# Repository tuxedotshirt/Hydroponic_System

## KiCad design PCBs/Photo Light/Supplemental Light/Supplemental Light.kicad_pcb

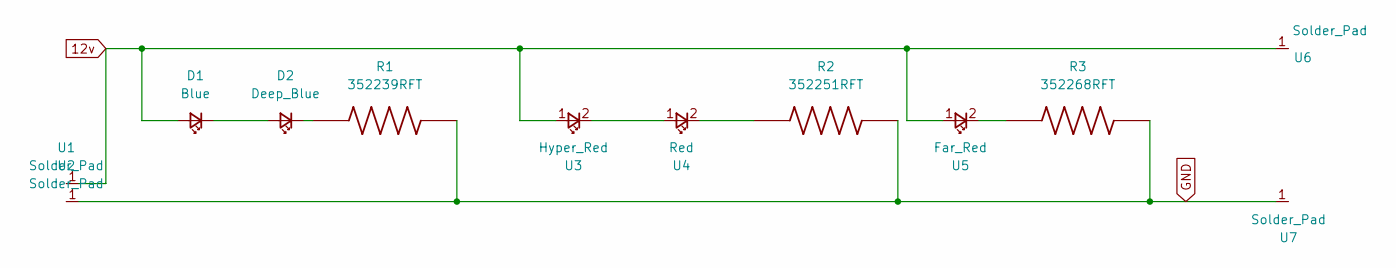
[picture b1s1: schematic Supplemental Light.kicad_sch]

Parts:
D1: Blue
D2: Deep_Blue; Deep Blue
R1: 352239RFT; RESC6332X120N
R2: 352251RFT; RESC6332X120N
R3: 352268RFT; RESC6332X120N
U1, U2, U6, U7: Solder_Pad; Solder Pad
U3: Hyper_Red; Hyper Red
U4: Red
U5: Far_Red; Far Red

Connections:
12v: D1.1 (A), U1.1, U3.1, U5.1, U6.1
GND: R1.2, R2.2, R3.2, U2.1, U7.1
unnamed: D1.2 (K), D2.1 (A)
unnamed: D2.2 (K), R1.1
unnamed: R2.1, U4.2
unnamed: U3.2, U4.1
unnamed: R3.1, U5.2

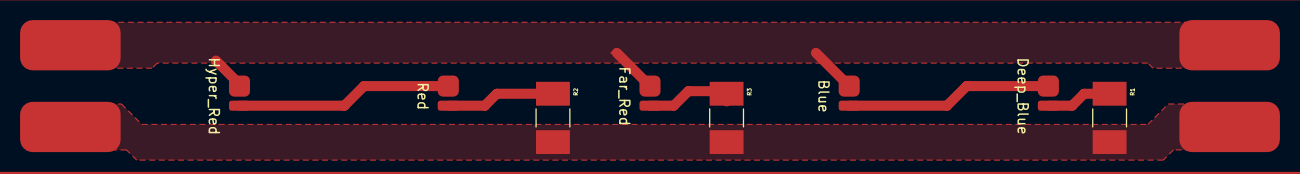
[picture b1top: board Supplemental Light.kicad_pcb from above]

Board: 2 copper layers, 12 parts (0 on the bottom side), 7 nets.

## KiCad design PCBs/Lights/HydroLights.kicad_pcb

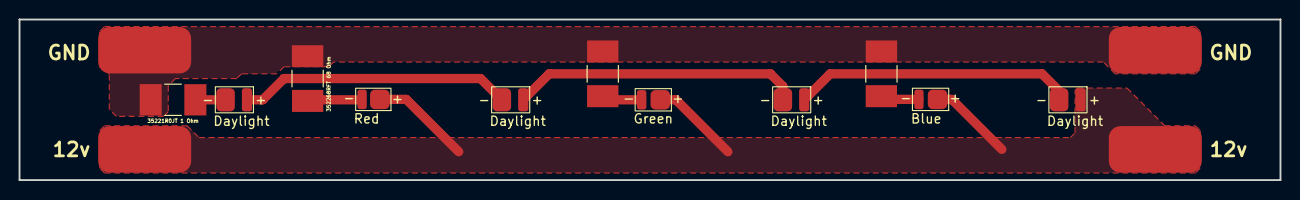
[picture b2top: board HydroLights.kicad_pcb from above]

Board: 2 copper layers, 135.6 x 17.3 mm, 15 parts (0 on the bottom side), 9 nets.

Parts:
R1: 352268RFT 68 Ohm; RESC6332X120N
R2, R4: 352262RFT 62 Ohm; RESC6332X120N
R3: 35221R0JT 1 Ohm; RESC6332X120N
U1, U2, U10, U11: Solder_Pad; Solder Pad
U3, U5, U7, U9: Daylight; 158303250A(Daylight)
U4: Red; 150283HS73103(Red)
U6: Blue; 150283BS73103(Blue)
U8: Green; 150283BS73103(Green)

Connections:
12v: U1.1, U3.2, U4.1, U6.1, U8.1, U10.1
GND: R1.2, R2.2, R3.1, R4.2, U2.1, U11.1
unnamed: R1.1, U4.2
unnamed: R2.1, U6.2
unnamed: R3.2, U9.1
unnamed: R4.1, U8.2
unnamed: U3.1, U5.2
unnamed: U5.1, U7.2
unnamed: U7.1, U9.2

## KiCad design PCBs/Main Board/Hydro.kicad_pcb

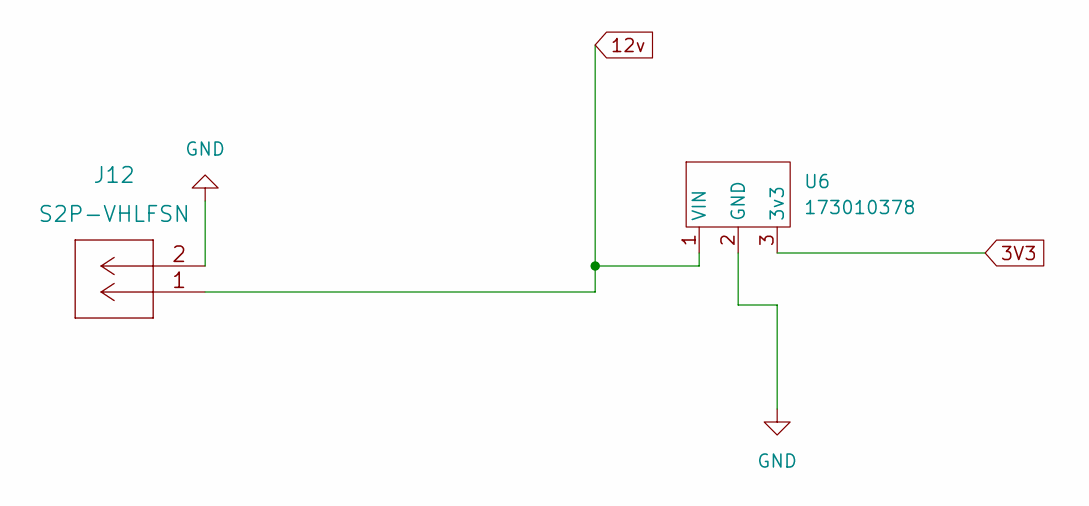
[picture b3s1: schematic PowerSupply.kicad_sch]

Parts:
J12: S2P-VHLFSN
U6: 173010378

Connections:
3V3: U6.3 (3v3); also elsewhere on the board
12v: J12.1, U6.1 (VIN); also elsewhere on the board
GND: J12.2, U6.2 (GND); also elsewhere on the board

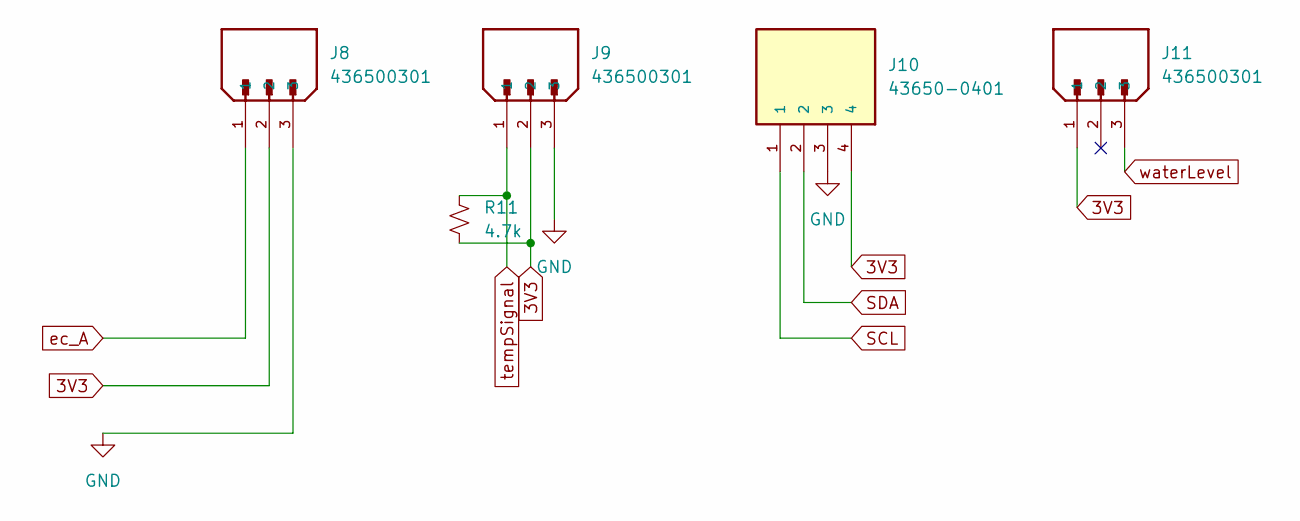
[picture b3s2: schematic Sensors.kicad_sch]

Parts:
J8, J9, J11: 436500301; MOLEX_436500301; PARTREV D7
J10: 43650-0401; MOLEX_43650-0401; PARTREV D7
R11: 4.7k; R_Axial_DIN0204_L3.6mm_D1.6mm_P7.62mm_Horizontal

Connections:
3V3: J8.2, J9.2, J10.4, J11.1, R11.2; also elsewhere on the board
GND: J8.3, J9.3, J10.3; also elsewhere on the board
SCL: J10.1; also elsewhere on the board
SDA: J10.2; also elsewhere on the board
ec_A: J8.1; also elsewhere on the board
tempSignal: J9.1, R11.1; also elsewhere on the board
waterLevel: J11.3; also elsewhere on the board

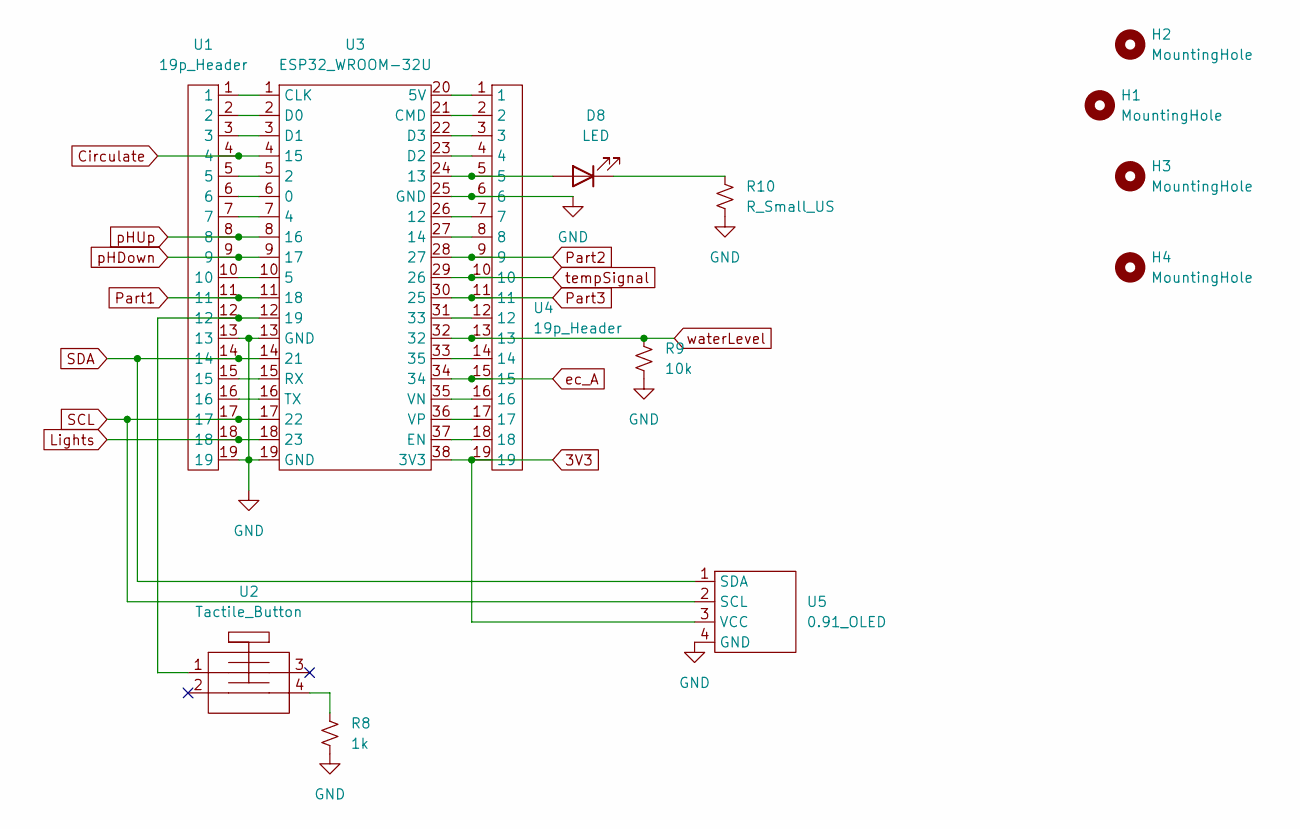
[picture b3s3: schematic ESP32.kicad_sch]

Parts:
D8: LED; LED_D5.0mm
H1, H2, H3, H4: MountingHole; Mounting Hole
R8: 1k; R_Axial_DIN0204_L3.6mm_D1.6mm_P7.62mm_Horizontal
R9: 10k; R_Axial_DIN0204_L3.6mm_D1.6mm_P7.62mm_Horizontal
R10: R_Small_US; R_Axial_DIN0204_L3.6mm_D1.6mm_P7.62mm_Horizontal
U1, U4: 19p_Header; 19p Header
U2: Tactile_Button
U3: ESP32_WROOM-32U; ESP32-WROOM-32U
U5: 0.91_OLED; 0.91 OLED

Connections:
3V3: U3.38 (3V3), U4.19, U5.3 (VCC); also elsewhere on the board
Circulate: U1.4, U3.4 (15); also elsewhere on the board
GND: R8.2, R9.2, R10.2, U1.13, U1.19, U3.13 (GND), U3.19 (GND), U3.25 (GND), U4.6, U5.4 (GND); also elsewhere on the board
Lights: U1.18, U3.18 (23); also elsewhere on the board
unnamed: D8.1 (K), R10.1
unnamed: D8.2 (A), U3.24 (13), U4.5
unnamed: R8.1, U2.4
unnamed: U1.1, U3.1 (CLK)
unnamed: U1.2, U3.2 (D0)
unnamed: U1.3, U3.3 (D1)
unnamed: U1.5, U3.5 (2)
unnamed: U1.6, U3.6 (0)
unnamed: U1.7, U3.7 (4)
unnamed: U1.10, U3.10 (5)
unnamed: U1.12, U2.1, U3.12 (19)
unnamed: U1.15, U3.15 (RX)
unnamed: U1.16, U3.16 (TX)
unnamed: U3.20 (5V), U4.1
unnamed: U3.21 (CMD), U4.2
unnamed: U3.22 (D3), U4.3
unnamed: U3.23 (D2), U4.4
unnamed: U3.26 (12), U4.7
unnamed: U3.27 (14), U4.8
unnamed: U3.31 (33), U4.12
unnamed: U3.33 (35), U4.14
unnamed: U3.35 (VN), U4.16
unnamed: U3.36 (VP), U4.17
unnamed: U3.37 (EN), U4.18
Part1: U1.11, U3.11 (18); also elsewhere on the board
Part2: U3.28 (27), U4.9; also elsewhere on the board
Part3: U3.30 (25), U4.11; also elsewhere on the board
SCL: U1.17, U3.17 (22), U5.2 (SCL); also elsewhere on the board
SDA: U1.14, U3.14 (21), U5.1 (SDA); also elsewhere on the board
ec_A: U3.34, U4.15; also elsewhere on the board
pHDown: U1.9, U3.9 (17); also elsewhere on the board
pHUp: U1.8, U3.8 (16); also elsewhere on the board
tempSignal: U3.29 (26), U4.10; also elsewhere on the board
waterLevel: R9.1, U3.32, U4.13; also elsewhere on the board

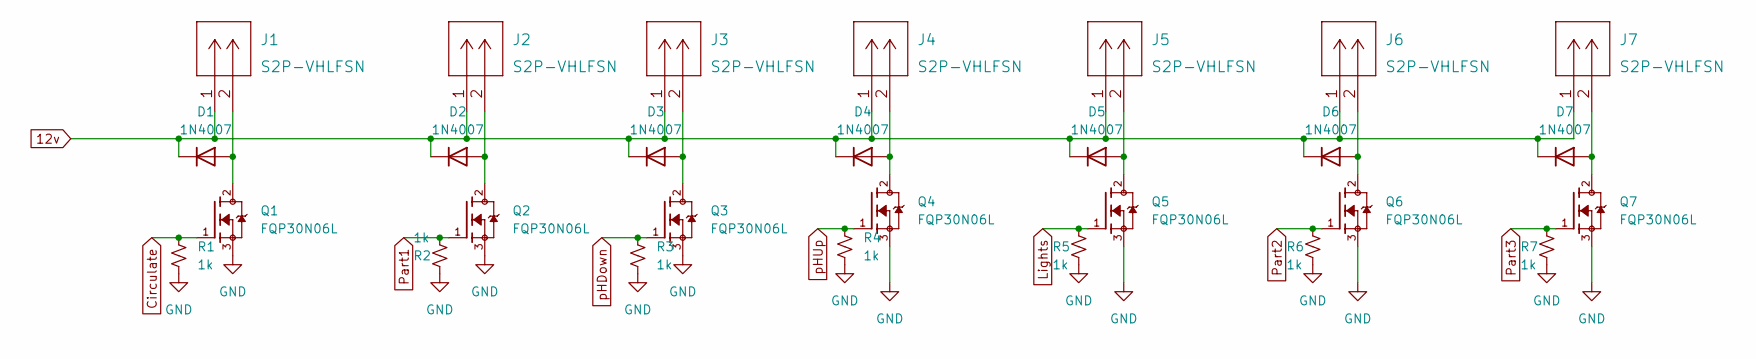
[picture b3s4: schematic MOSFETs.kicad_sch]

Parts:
D1, D2, D3, D4, D5, D6, D7: 1N4007; D_DO-41_SOD81_P10.16mm_Horizontal
J1, J2, J3, J4, J5, J6, J7: S2P-VHLFSN
Q1, Q2, Q3, Q4, Q5, Q6, Q7: FQP30N06L; TO220V
R1, R2, R3, R4, R5, R6, R7: 1k; R_Axial_DIN0207_L6.3mm_D2.5mm_P7.62mm_Horizontal

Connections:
12v: D1.1 (K), D2.1 (K), D3.1 (K), D4.1 (K), D5.1 (K), D6.1 (K), D7.1 (K), J1.1, J2.1, J3.1, J4.1, J5.1, J6.1, J7.1; also elsewhere on the board
Circulate: Q1.1, R1.1; also elsewhere on the board
GND: Q1.3, Q2.3, Q3.3, Q4.3, Q5.3, Q6.3, Q7.3, R1.2, R2.2, R3.2, R4.2, R5.2, R6.2, R7.2; also elsewhere on the board
Lights: Q5.1, R5.1; also elsewhere on the board
unnamed: D1.2 (A), J1.2, Q1.2
unnamed: D2.2 (A), J2.2, Q2.2
unnamed: D3.2 (A), J3.2, Q3.2
unnamed: D4.2 (A), J4.2, Q4.2
unnamed: D5.2 (A), J5.2, Q5.2
unnamed: D6.2 (A), J6.2, Q6.2
unnamed: D7.2 (A), J7.2, Q7.2
Part1: Q2.1, R2.1; also elsewhere on the board
Part2: Q6.1, R6.1; also elsewhere on the board
Part3: Q7.1, R7.1; also elsewhere on the board
pHDown: Q3.1, R3.1; also elsewhere on the board
pHUp: Q4.1, R4.1; also elsewhere on the board

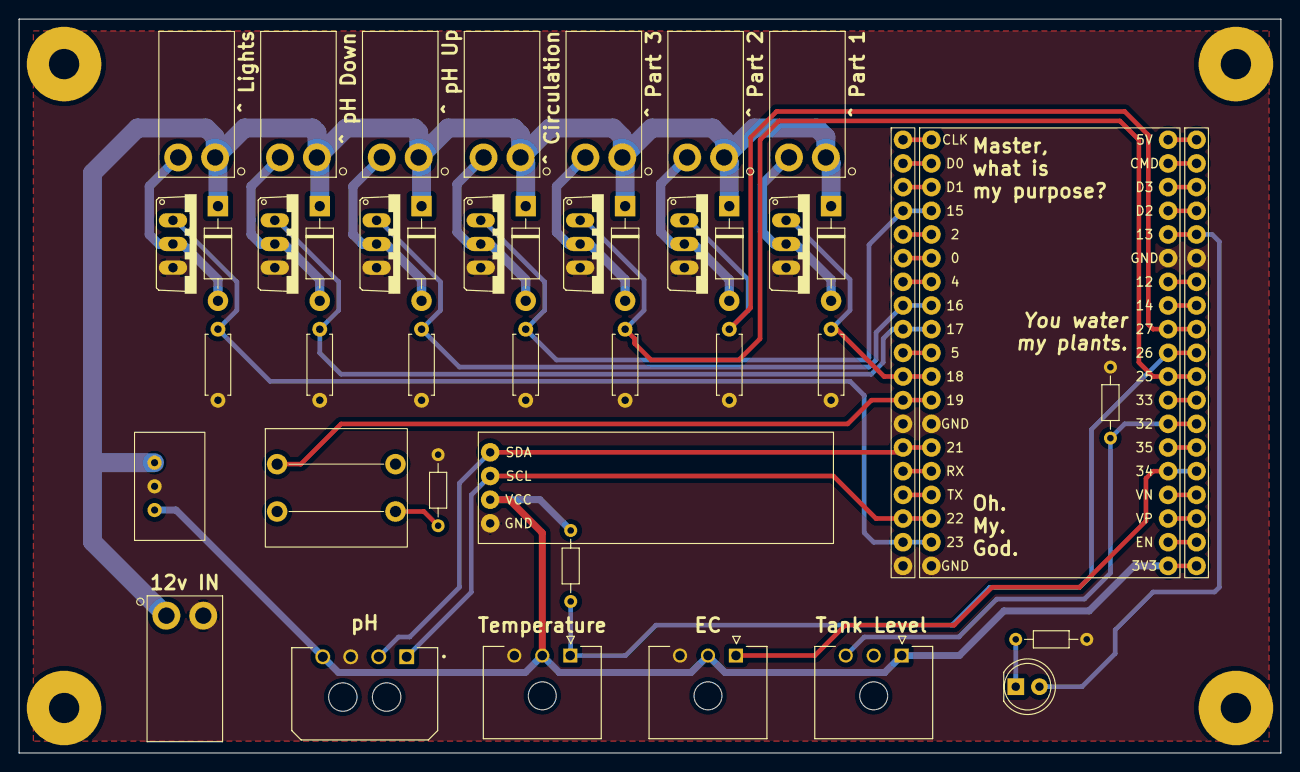
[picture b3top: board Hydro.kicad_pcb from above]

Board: 2 copper layers, 135.4 x 78.7 mm, 48 parts (0 on the bottom side), 46 nets.

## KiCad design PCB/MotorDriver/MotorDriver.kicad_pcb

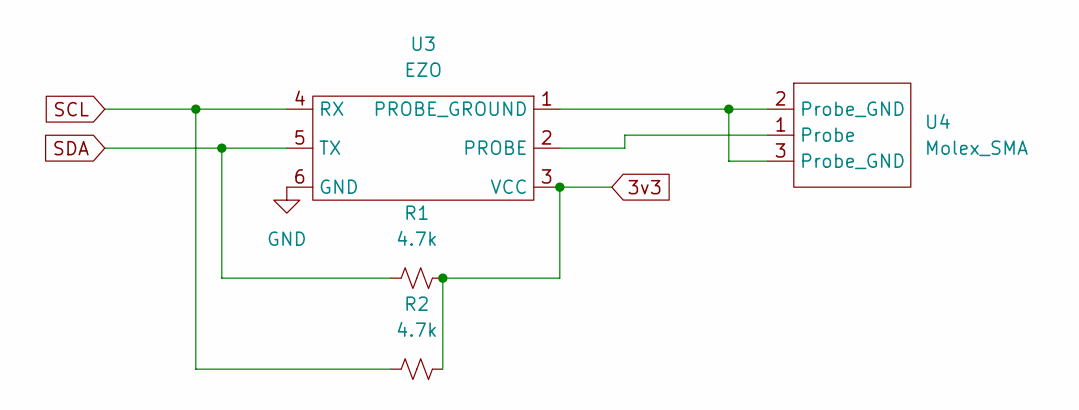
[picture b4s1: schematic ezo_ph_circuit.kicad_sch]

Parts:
R1, R2: 4.7k; R_Axial_DIN0207_L6.3mm_D2.5mm_P10.16mm_Horizontal
U3: EZO
U4: Molex_SMA; Molex SMA

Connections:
3v3: R1.1, R2.1, U3.3 (VCC); also elsewhere on the board
GND: U3.6 (GND); also elsewhere on the board
unnamed: U3.1 (PROBE_GROUND), U4.2 (Probe_GND), U4.3 (Probe_GND)
unnamed: U3.2 (PROBE), U4.1 (Probe)
SCL: R2.2, U3.4 (RX); also elsewhere on the board
SDA: R1.2, U3.5 (TX); also elsewhere on the board

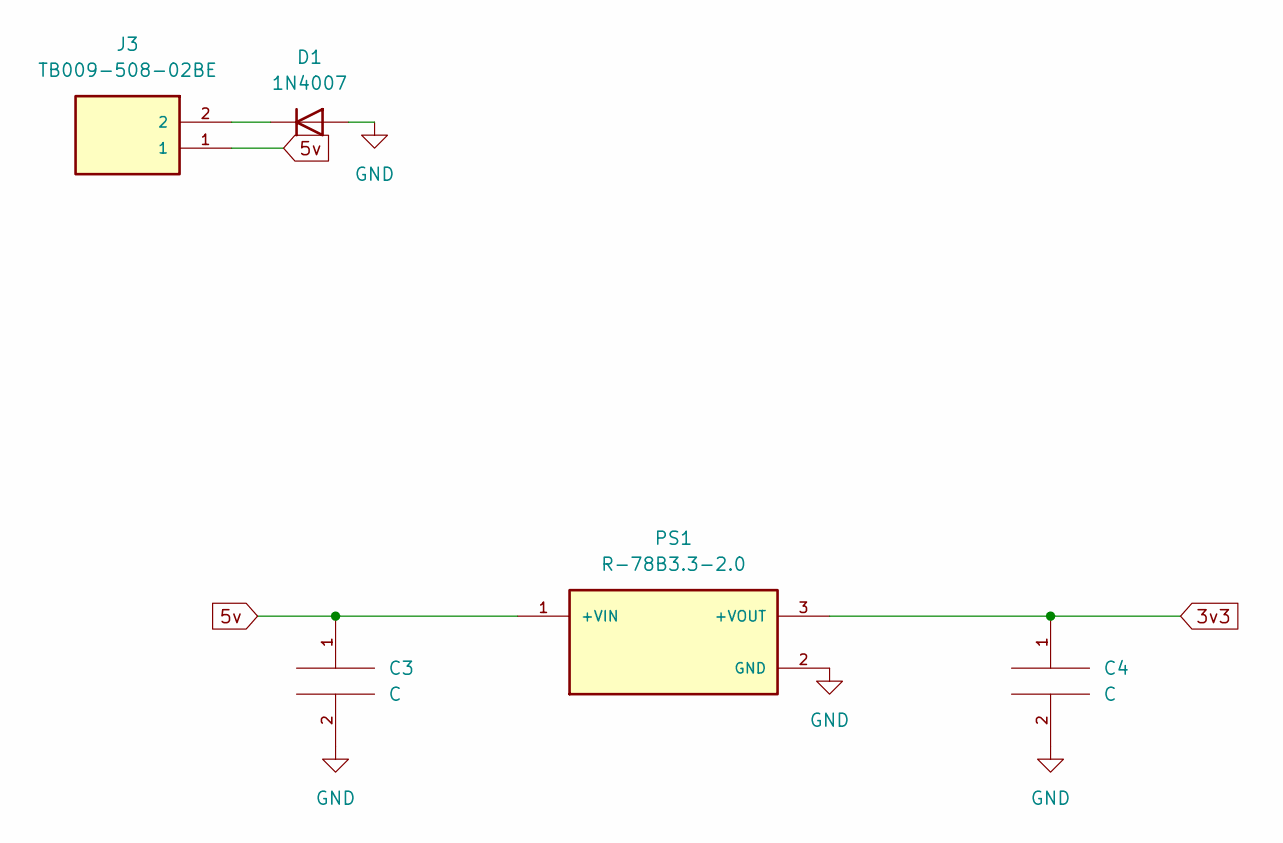
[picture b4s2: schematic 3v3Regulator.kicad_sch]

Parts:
C3, C4: C; C_Disc_D5.0mm_W2.5mm_P5.00mm
D1: 1N4007; D_DO-41_SOD81_P10.16mm_Horizontal
J3: TB009-508-02BE; CUI_TB009-508-02BE
PS1: R-78B3.3-2.0; CONV_R-78B3.3-2.0

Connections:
3v3: C4.1, PS1.3 (+VOUT); also elsewhere on the board
5v: C3.1, J3.1, PS1.1 (+VIN); also elsewhere on the board
GND: C3.2, C4.2, D1.2 (A), PS1.2 (GND); also elsewhere on the board
unnamed: D1.1 (K), J3.2

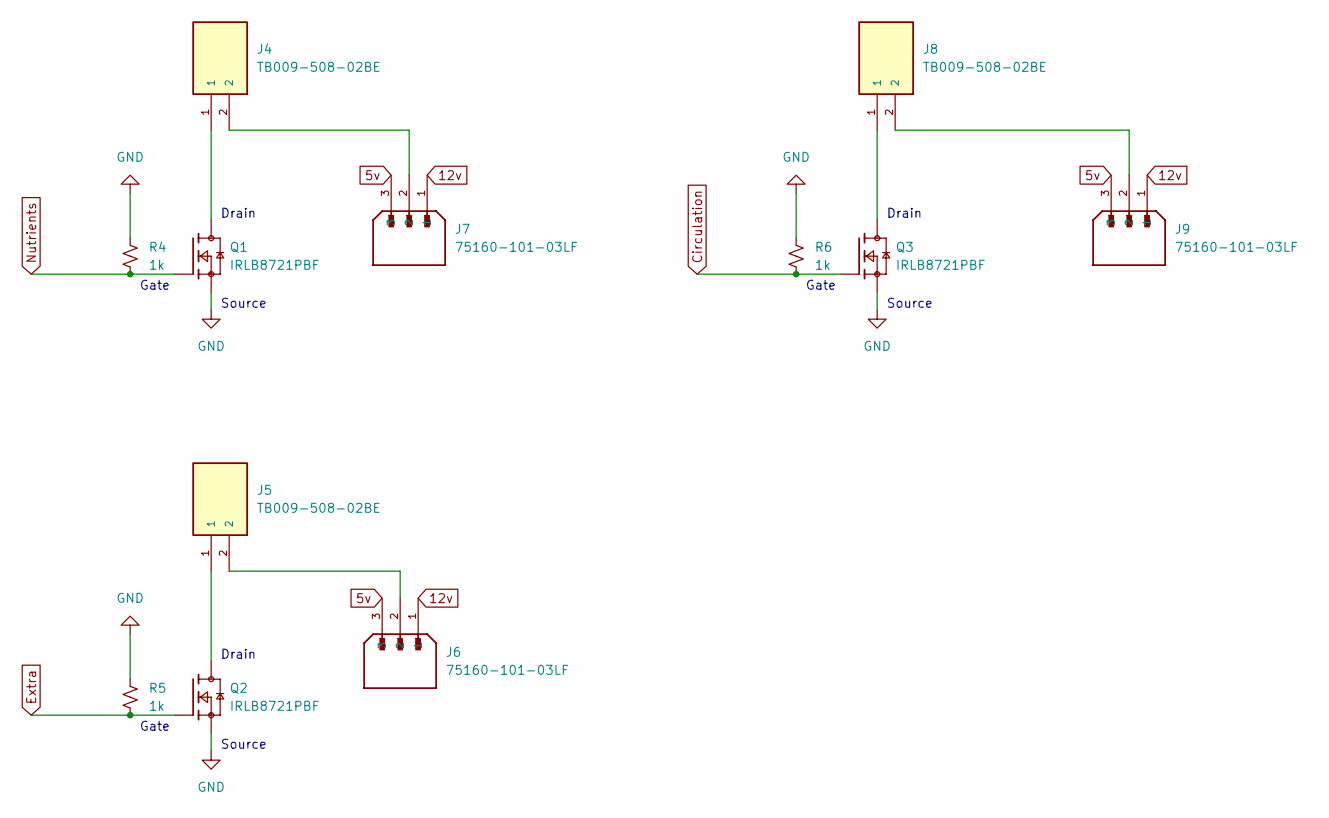
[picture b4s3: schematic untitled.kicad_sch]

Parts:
J4, J5, J8: TB009-508-02BE; CUI_TB009-508-02BE
J6, J7, J9: 75160-101-03LF; AMPHENOL_75160-101-03LF; PARTREV BW
Q1, Q2, Q3: IRLB8721PBF; TO254P1067X483X2057-3; PARTREV 4/22/09
R4, R5, R6: 1k; R_Axial_DIN0207_L6.3mm_D2.5mm_P10.16mm_Horizontal

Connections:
5v: J6.3, J7.3, J9.3; also elsewhere on the board
12v: J6.1, J7.1, J9.1
Circulation: Q3.1, R6.2
Extra: Q2.1, R5.2
GND: Q1.3, Q2.3, Q3.3, R4.1, R5.1, R6.1; also elsewhere on the board
unnamed: J4.1, Q1.2
unnamed: J4.2, J7.2
unnamed: J5.1, Q2.2
unnamed: J5.2, J6.2
unnamed: J8.1, Q3.2
unnamed: J8.2, J9.2
Nutrients: Q1.1, R4.2

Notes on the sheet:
Source
Gate
Drain

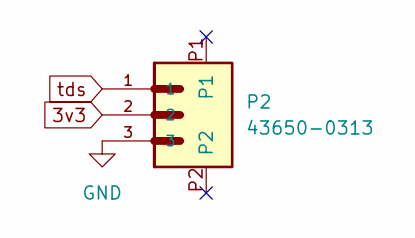
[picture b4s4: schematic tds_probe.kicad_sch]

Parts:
P2: 43650-0313; MOLEX_43650-0313

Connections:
3v3: P2.2; also elsewhere on the board
GND: P2.3; also elsewhere on the board
tds: P2.1; also elsewhere on the board

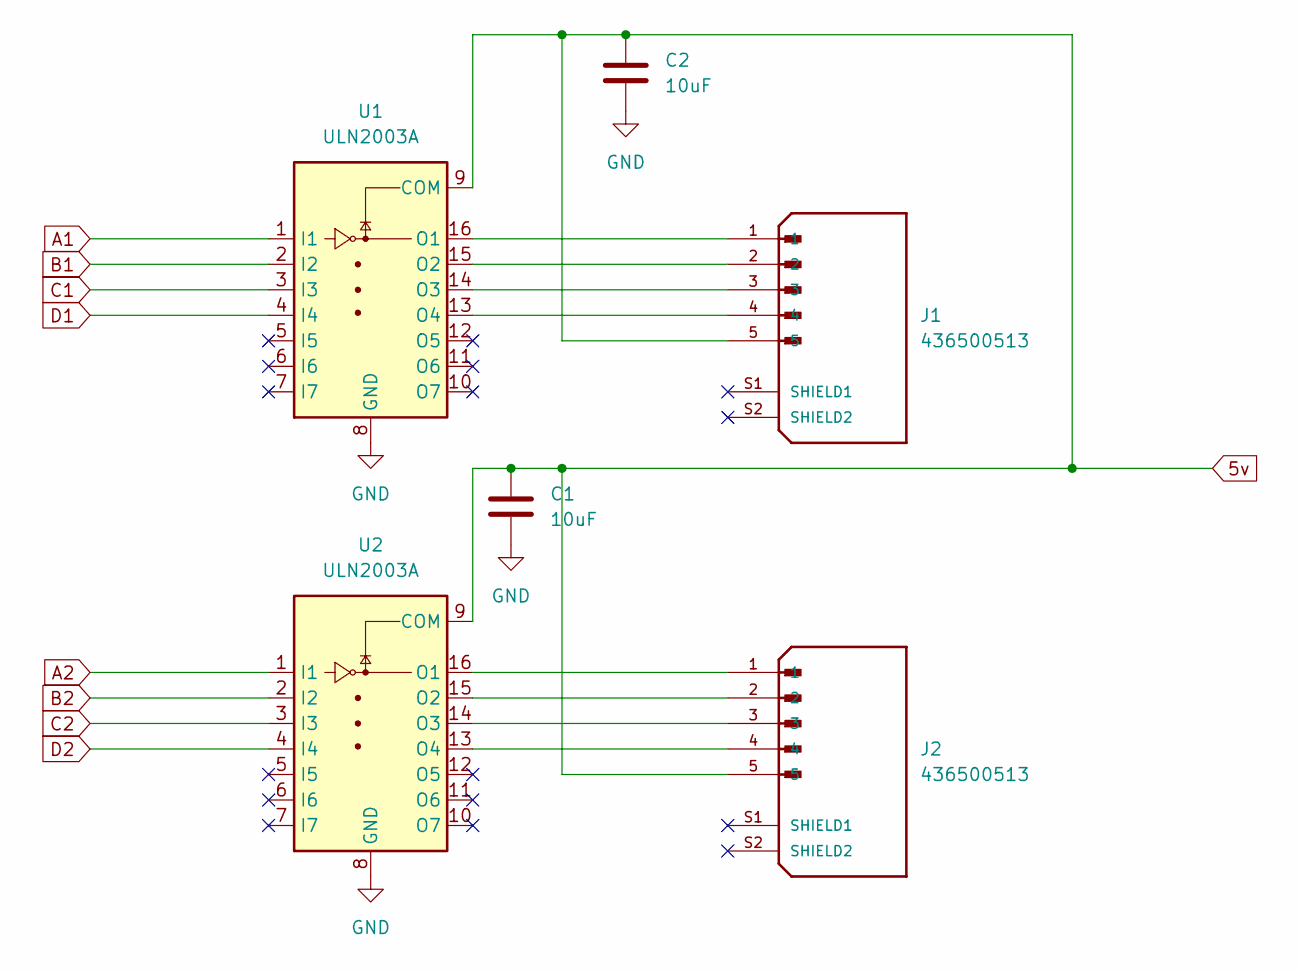
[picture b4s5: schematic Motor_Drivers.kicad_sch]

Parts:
C1, C2: 10uF; C_Disc_D5.0mm_W2.5mm_P5.00mm
J1, J2: 436500513; MOLEX_436500513; PARTREV E8
U1, U2: ULN2003A; DIP-16_W7.62mm_Socket

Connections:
5v: C1.1, C2.1, J1.5, J2.5, U1.9 (COM), U2.9 (COM); also elsewhere on the board
A1: U1.1 (I1); also elsewhere on the board
A2: U2.1 (I1); also elsewhere on the board
B1: U1.2 (I2); also elsewhere on the board
B2: U2.2 (I2); also elsewhere on the board
C1: U1.3 (I3); also elsewhere on the board
C2: U2.3 (I3); also elsewhere on the board
D1: U1.4 (I4); also elsewhere on the board
D2: U2.4 (I4); also elsewhere on the board
GND: C1.2, C2.2, U1.8 (GND), U2.8 (GND); also elsewhere on the board
unnamed: J1.1, U1.16 (O1)
unnamed: J1.2, U1.15 (O2)
unnamed: J1.3, U1.14 (O3)
unnamed: J1.4, U1.13 (O4)
unnamed: J2.1, U2.16 (O1)
unnamed: J2.2, U2.15 (O2)
unnamed: J2.3, U2.14 (O3)
unnamed: J2.4, U2.13 (O4)

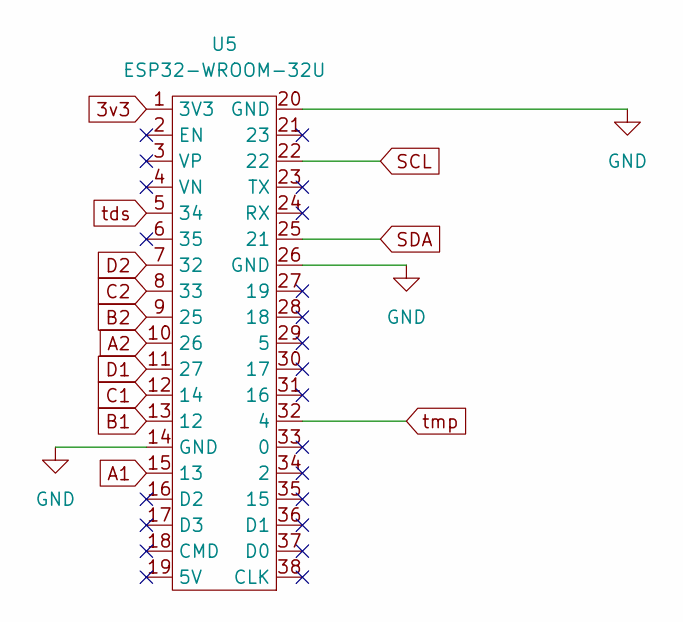
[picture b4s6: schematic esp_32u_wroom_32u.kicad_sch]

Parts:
U5: ESP32-WROOM-32U

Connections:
3v3: U5.1 (3V3); also elsewhere on the board
A1: U5.15 (13); also elsewhere on the board
A2: U5.10 (26); also elsewhere on the board
B1: U5.13 (12); also elsewhere on the board
B2: U5.9 (25); also elsewhere on the board
C1: U5.12 (14); also elsewhere on the board
C2: U5.8 (33); also elsewhere on the board
D1: U5.11 (27); also elsewhere on the board
D2: U5.7 (32); also elsewhere on the board
GND: U5.14 (GND), U5.20 (GND), U5.26 (GND); also elsewhere on the board
SCL: U5.22; also elsewhere on the board
SDA: U5.25 (21); also elsewhere on the board
tds: U5.5 (34); also elsewhere on the board
tmp: U5.32 (4); also elsewhere on the board

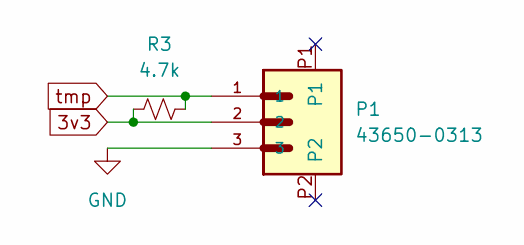
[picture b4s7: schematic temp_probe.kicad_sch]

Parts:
P1: 43650-0313; MOLEX_43650-0313
R3: 4.7k; R_Axial_DIN0207_L6.3mm_D2.5mm_P10.16mm_Horizontal

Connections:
3v3: P1.2, R3.2; also elsewhere on the board
GND: P1.3; also elsewhere on the board
tmp: P1.1, R3.1; also elsewhere on the board

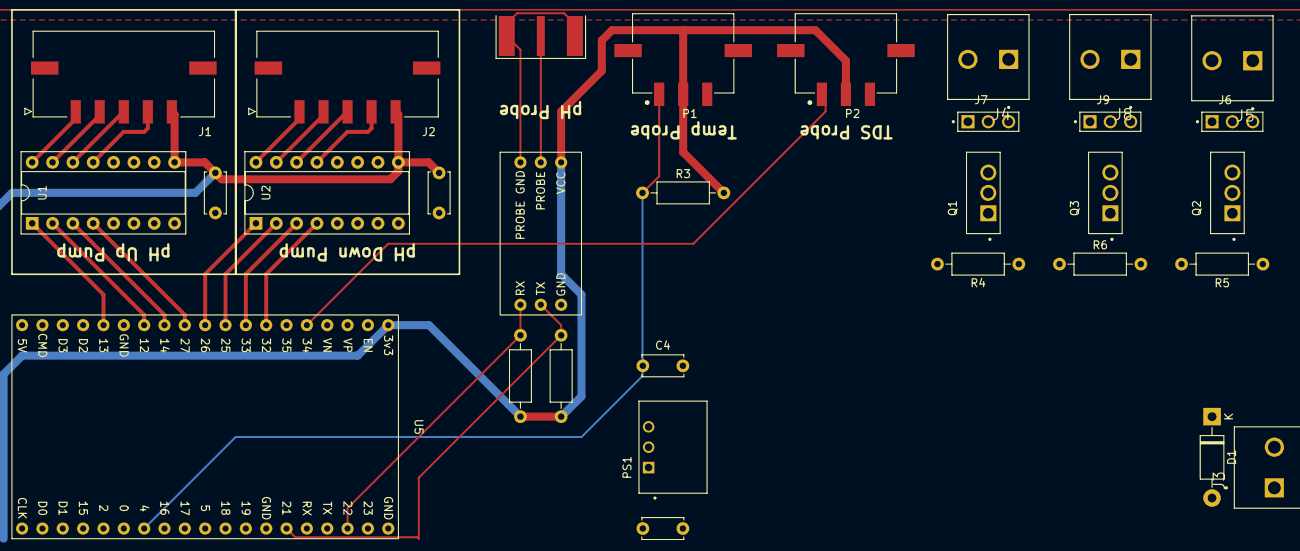
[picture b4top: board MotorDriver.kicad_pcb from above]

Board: 2 copper layers, 31 parts (0 on the bottom side), 36 nets.

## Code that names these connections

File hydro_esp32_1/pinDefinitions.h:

//Pin definitions

#define circulation 15
#define pHUp 16
#define pHDown 17
#define part1 18
#define lights 23
#define part2 27
#define part3 25
#define errorLED 13
#define SW 19
#define waterLevel 32

#define TdsSensorPin 34
#define oneWireBus 26

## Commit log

2022-12-27 Documentation
2023-01-01 Add wifi and DB
2023-01-23 Fix WIFI and BLE bug
2023-01-23 Add BLE indicator LED
2023-04-08 PCB Update
2023-04-17 Remove steppers, add OLED
2023-04-17 update pcb
2023-04-20 Finished PCBs
2023-04-21 Update blocking calls, remove cipher
2023-04-22 Small update
2023-04-23 Cleaned up ntp time
2023-04-24 Working on settings menu
2023-04-25 Work on settings menu
2023-04-27 Changed some pins
2023-04-29 Error LED code update
2023-05-04 changed semaphore wait to ms
2023-05-09 Changes to PCB, wired sensors to board
2023-05-16 Finished EC and pH probe calibration
2023-05-21 PCB changes
2023-07-16 Document Cleanup
2023-07-18 Update SimpleTimer
2023-07-18 Remove unused files
2023-07-18 Added SimpleTimer to repo
2023-07-18 Fix git subcomponent issue
2023-07-18 Arduino IDE branch test
2023-08-07 update values
2023-08-13 Move default values
2023-08-30 First Live Run
2023-08-30 Fix lightOnTime error
2023-11-12 Testing pH probe errors
2023-11-15 Fix pH probe calibration to work with I2C
    No examples or datasheet for I2C communication besides taking a reading. Figured it out. Fixed electrical interference with pH probe.
2023-11-28 Add printable assets
2023-12-05 New lights
2023-12-10 Work on lights
2023-12-20 code organization
2024-01-08 refactor

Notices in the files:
parts and their libraries:
Copyright 2021 Accelerated Designs. All rights reserved.
